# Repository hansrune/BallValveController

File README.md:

# Ball Valve Controller

A DYI ball valve controller for CR05 wiring based on ESP32c3. This device is mainly intended for irrigation and main water valve automation, but is also very suitable for water leak prevention. For safety, a battery helps make sure the device returns to its default state upon reset or power failure. The device can be directly controlled to the default state by external signals such as a local water leak sensor, or you can use your home automation system to cut off water supply based on more advanced conditions.

The default state can be normally open or normally closed, and is automatically detected on restart. The safety battery voltage is also monitored and available to read remotely.

This board is tested with ESPhome and ESPEasy [firmware](#firmwares) (build instructions below), and is easily used with home automation systems that support MQTT auto discovery, the native Home Assistant API, and the many [controllers that ESPEasy supports](https://espeasy.readthedocs.io/en/latest/Controller/_Controller.html)

## Introduction

Some of the main features and benefits

- **Supports 5-wire CR05 wiring**
    - The true state of the valve can be fed back to your automation system over WiFi
    - You can detect valve malfunctioning
    - Is used by the firmware to automatically detect NO (normally open) or NC (normally closed) operation during startup
- **Supports battery backup and battery status monitoring**
    - A 9V battery is sufficient to make sure the valve returns to it's default state during power failure and resets
    - The battery voltage is readable and available as a sensor
- **Water leak sensors and protection**
    - There are inputs to force the valve to the default state as well as the activated state. Typically used with a Fibaro water leak detector associates with a Fibaro smart implant so that the valve can be "overruled" without any host controller / home automation being involved. Numerous Z-wave and Zigbee devices support this.
- **1-wire support**
    - This is used to attach DS18B20 temperature sensor. I use this with a nearby water heater. Two inputs with pull-ups are available, but you can also use multiple sensors on one wire
- **I2C support**
    - An I2C pin header with power supply is available to use with I2C sensors
    - ... or you can use the same GPIO pins for any other purpose of your choise
- **WiFi based**
    - This is almost a must have for most home automation systems
    - OTA support
    - Configuration backup, restore and bulk updates.
- **Firmware of your choise**
    - ESPEasy with Domoticz over http. Device creation uses virtual sensors
    - ESPEasy with Domotics and Home Assistant via MQTT. Device creation uses a MQTT configuration text file.
    - ESPHome to Home Assistant via MQTT and auto discovery
    - ESPHome to Domoticz via MQTT and auto discovery
    - ... and as the hardware supports using both Arduino and ESP-IF development kits, almost any other firmware can be created.
- **Seed Studio XIAO ESP32C3**
    - This device is shielded and comes with an external IPX antenna connector
    - FCC and CE regulations approved

## Setup and mounting

A typical small electic junction box is used for an easy and affordable way for housing the PCB and battery. These boxes often also support using glands for humidity protection and strain releave.

Please note the positioning of the battery. The battery can be easily removed to provide room for a USB-C cable connection, in case an OTA update should fail. Failure to OTA is usually recovered by a power cycle, but bugs in OTA libaries need a physical connection for recovery.

The switch (see wiring below) is used to select between normally open and normally closed operation. As the ball valve will return to it's default position during reset, the valve position feedback switches are used to automatically determine if the setup is normally open or normally closed.

One of my permanent setups look like this:

... where the 1-wire sensors are attached to top and bottom of our electric water boiler.

## Indicators

The 5mm LEDs are suggested to be reverse mounted for the following purposes:

- LED D7 will indicate the state of valve activation - solid on or off
- LED D6
  - will blink with a duty cycle 1-4 or 4-1 to indicate valve closed or open
  - a duty cycle 1:1 will indicate a reset is ongoing
  - no change indicates out of power, device death/freeze or other

## Implementation and design

The easiest way to view the controller is probably this block level wiring diagram:

This is just a typical setup for the various external components. The schematic diagram is [available here](KiCad/BallValveController-schema-7.0.pdf). The [KiCad EDA](https://www.kicad.org/) project is in the [same folder](./KiCad)

If you use more than one 1-wire sensor, it is easier in ESPHome to use both inputs (RX+TX in diagram) with automatic sensor address detection.

### GPIO pin usage

| PIN      | Capabilty          | Function                            |
|----------|--------------------|-------------------------------------|
| GPIO2    | Active low out     | Activate battery read               |
| GPIO3/A1 | Analog in          | Battery read input                  |
| GPIO4    | Active low in      | Valve open                          |
| GPIO5    | Active low in      | Valve closed                        |
| GPIO6    | I2C                | SDA                                 |
| GPIO7    | I2C                | SCL                                 |
| GPIO9    | Active low out     | Internal status LED                 |
| GPIO10   | Active high out    | Valve activate to non-default state |
| GPIO20   | RX / 1-wire        | Serial or 1-wire sensor             |
| GPIO21   | TX / 1-wire        | Serial or 1-wire sensor             |

### Interfacing leak detectors

J10 is used to interface leak detectors:

| PIN  | Name       | Function                              |
|------|------------|---------------------------------------|
| 1    | Activate   | Pull high to force non-default state  |
| 2    | Deactivate | Battery read input                    |
| 3    | Vcc        | Supply voltage, 3.3V, 5V or 12V strap |
| 4    | GND        | Ground                                |

#### Connecting a Fibaro Implant

A Fibaro implant may be associated with Fibaro leak detector(s). This type of device to device can work even without the Z-Wave hub being operational

- `VCC` - strap JP1 to the 12V supply as illustrated [here](#known-bugs), or just feed the Implant directly from the 12V power supply
- `Deactivate` - connect to one side of Out1 - the other side to GND
- `GND` for implant power and Out1

#### Connecting an Arduino water leak sensor

Typical Arduino water leak detectors are open collector outputs. Connect as follows:

- `VCC` - strap/solder JP1 to the 3.3V side for sensor power 
- `Deactivate` - connect to sensor output. This will force the valve to default state when activated
- `GND` - sensor power ground

## Hardware - getting started

This project uses my [KiCad-lib-ESP32 repository](https://github.com/hansrune/KiCad-lib-ESP32.git) as a [git submodule](https://www.git-scm.com/book/en/v2/Git-Tools-Submodules). To check this out, use the following:

```bash
git clone --recurse-submodules https://github.com/hansrune/BallValveController.git 
```

### Materials used

This project uses the [Seed Studio XIAO ESP32C3 RISC-V module](https://www.seeedstudio.com/Seeed-XIAO-ESP32C3-p-5431.html). This tiny device has proven to be more reliable than most ESP8266 modules used in earlier versions. This module also comes with an IPX connector for connecting an external antenna, and is delivered with a simple external antenna for good range. This device is also EMI shielded and certified.

A ball valve like [these HSH-FLO valves](https://www.ebay.com/itm/121728665101?var=420727385309) uses metal gears, and also have a manual override possibility. Despite the moderate cost, I have found them very reliable. Manufacturer claims 100k operations. I typically use a 2 or some times 3-port version, size 3/4" DN20, DC12/24V and with CR05-01 wiring, including a manual overrride whell option.

Any available 12V DC power supply delivering 1A or more should do.

There are many options and possible pinouts for DC-DC converters for the 12V to 5V conversion. A linear regulator (L7805) will need a heatsink, so a DC-DC converter is recommended.

The MOSFETs need a low Vgs trigger voltage, i.e. well under 3V on full load. I have used Si2301/A1SHB for the P-channel, and Si2302/N025P for the N-channel, and 2N2222/1P - all SOT-23 packages.

Resistors are 0805 size. Screw terminals are 3.5mm, which is a tight fit when ferrules are being used.

For more information, use [this KiCad BOM](KiCad/BallValveController-BOM.csv)

## Hardware assembly

Soldering a prototype by hand is possible if you have a steady hand and a small solder iron tip. A microscope is recommended to inspect the solder joints properly.

Recommend to do the SMD parts first, then other components. I prefer to mount the 5mm LEDs on the back side.

### Hardware tests

You should test at least the following **before adding the ESP32 module**:

- Attach a battery and check that the valve can be operated both NO and NC
- Add power and check that 5V conversion is OK
- Apply 5V to the ESP32c3 pin 11 to check that the relay is operated
- Apply 0V to pin 1 of the ESP32c3 and check that pin 2 receives a 200ms readout of the battery voltage (divided by the 68k + 20k resistors)

## Firmwares

### ESPHome

ESPHome firmware can be set up from [this ESPHome configuration repository](https://github.com/hansrune/esphome-config) using the `test_ball_valve` as a template

Follow the [README](https://github.com/hansrune/esphome-config) for instructions on what you will likely want to change.

By default, MQTT auto discovery is being used. This should work out of the box with Home Assistant, Domoticz and other that support [Home Assistant MQTT Auto Discovery](https://www.home-assistant.io/integrations/mqtt/#mqtt-discovery)

In Home Assistant, the device has these controls:

... and information / diagnostics panel:

### ESPEasy

ESPEasy can be used with a number of different controllers / home automation systms. A custom firmware build description is [available here](https://github.com/hansrune/ESPEasy-custom/blob/builds/custom/mega-20240822-1/README-custombuilds.md)

ESPEasy requires many settings. For configuration settings and rule files, you can upload the files from [this page](./ESPEasy/) as a starting point. Please make sure to change name, unit number, controller IP addresses, NTP, syslog host and latitude/longitude. This configuration uses both a MQTT controller and a Domoticz controller. Change to what you need.

## Bugs and tweaks

### For Fibaro Smart Implants

A Fibaro Smart implant needs a 9-30V power supply. To accomodate that, you can supply 12V by running a wire on the back of the PCB as follows:

... or just connect to the 12V input terminal

<!-- 

## How to contribute

-->

## License

This project is licensed under the [GNU General Public License v3.0](GNU-LICENSE-V3.txt) for the software, [CERN-OHL-W](OHL-LICENSE.txt) for the hardware, and [CC BY-SA](CC-BY-SA-LICENCE.txt) for the documentation and ideas.

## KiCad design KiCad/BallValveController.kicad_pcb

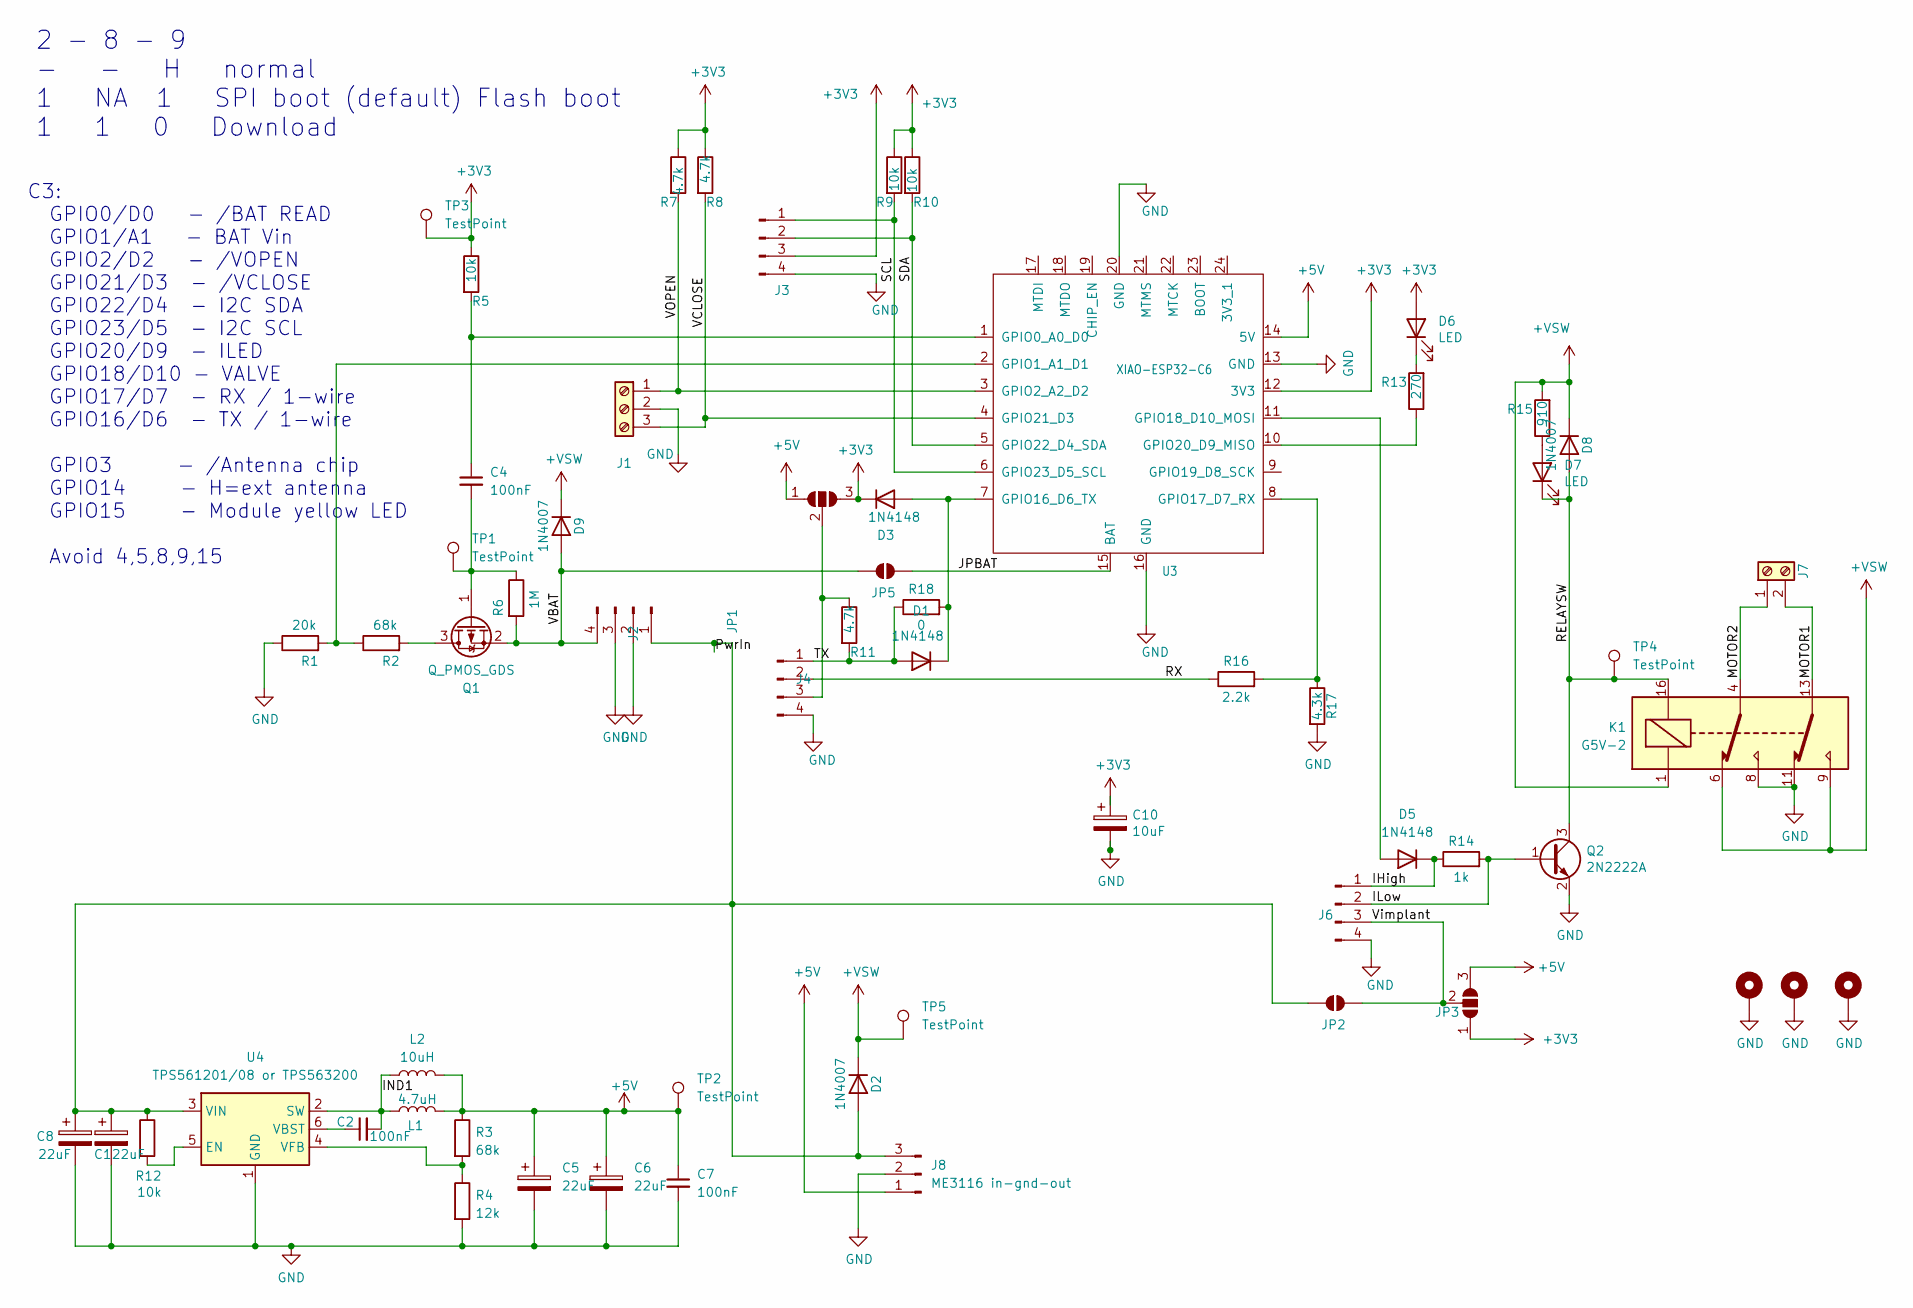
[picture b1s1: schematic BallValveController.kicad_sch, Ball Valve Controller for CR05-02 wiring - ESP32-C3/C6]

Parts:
C1, C8: 22uF; C_1206_3216Metric_Pad1.33x1.80mm_HandSolder
C2, C4, C7: 100nF; C_0805_2012Metric_Pad1.18x1.45mm_HandSolder
C5, C6: 22uF; C_1206_3216Metric_Pad1.33x1.80mm_HandSolder; JLCPCB Part# C45783
C10: 10uF; C_1206_3216Metric_Pad1.33x1.80mm_HandSolder
D1, D3, D5: 1N4148; D_SOD-323_HandSoldering
D2, D8, D9: 1N4007; D_SOD-123
D6, D7: LED; LED_D3.0mm_Clear
H1, H2, H3: MountingHole_Pad; MountingHole_3.2mm_M3_ISO14580_Pad
J1: Screw_Terminal_01x03; TerminalBlock_Phoenix_PT-1,5-3-3.5-H_1x03_P3.50mm_Horizontal
J2, J4, J6: Screw_Terminal_01x04; TerminalBlock_Phoenix_PT-1,5-4-3.5-H_1x04_P3.50mm_Horizontal
J3: Screw_Terminal_01x04; PinHeader_1x04_P2.54mm_Vertical
J7: Screw_Terminal_01x02; TerminalBlock_Phoenix_PT-1,5-2-3.5-H_1x02_P3.50mm_Horizontal
J8: ME3116 in-gnd-out; PinHeader_1x03_P2.54mm_Vertical
JP1, JP3: SolderJumper_3_Open; SolderJumper-3_P1.3mm_Open_Pad1.0x1.5mm_NumberLabels
JP2, JP5: SolderJumper_2_Open; SolderJumper-2_P1.3mm_Open_RoundedPad1.0x1.5mm
K1: G5V-2; Relay_DPDT_Omron_G5V-2
L1: 4.7uH; L_2010_5025Metric_Pad1.52x2.65mm_HandSolder; JLCPCB Part# C2929438
L2: 10uH; L_Bourns-SRU8028_8.0x8.0mm; JLCPCB Part# C2929438
Q1: Q_PMOS_GDS; SOT-23
Q2: 2N2222A; SOT-23
R1: 20k; R_0805_2012Metric_Pad1.20x1.40mm_HandSolder
R2: 68k; R_0805_2012Metric_Pad1.20x1.40mm_HandSolder
R3: 68k; R_0805_2012Metric_Pad1.20x1.40mm_HandSolder; JLCPCB Part# C17850
R4: 12k; R_0805_2012Metric_Pad1.20x1.40mm_HandSolder; JLCPCB Part# C4328
R5, R9, R10: 10k; R_0805_2012Metric_Pad1.20x1.40mm_HandSolder
R6: 1M; R_0805_2012Metric_Pad1.20x1.40mm_HandSolder
R7, R8, R11: 4.7k; R_0805_2012Metric_Pad1.20x1.40mm_HandSolder
R12: 10k; R_0805_2012Metric_Pad1.20x1.40mm_HandSolder; JLCPCB Part# C4328
R13: 270; R_0805_2012Metric_Pad1.20x1.40mm_HandSolder
R14: 1k; R_0805_2012Metric_Pad1.20x1.40mm_HandSolder
R15: 910; R_0805_2012Metric_Pad1.20x1.40mm_HandSolder
R16: 2.2k; R_0805_2012Metric_Pad1.20x1.40mm_HandSolder
R17: 4.3k; R_0805_2012Metric_Pad1.20x1.40mm_HandSolder
R18: 0; R_0805_2012Metric_Pad1.20x1.40mm_HandSolder
TP1, TP2, TP3, TP4, TP5: TestPoint; TestPoint_THTPad_D1.0mm_Drill0.5mm
U3: XIAO-ESP32-C6; XIAO-ESP32-C3C6-SMD
U4: TPS561201/08 or TPS563200; SOT-23-6

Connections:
+3V3: C10.1, D3.1 (K), D6.2 (A), J3.3, JP1.3 (B), JP3.1 (A), R5.1, R7.1, R8.1, R9.1, R10.1, TP3.1 (1_1), U3.12 (3V3)
+5V: C5.1, C6.1, C7.1, J8.1, JP1.1 (A), JP3.3 (B), L1.2, L2.2, R3.1, TP2.1 (1_1), U3.14 (5V)
+VSW: D2.1 (K), D8.1 (K), D9.1 (K), K1.1, K1.6, K1.9, R15.2, TP5.1 (1_1)
/IHigh: D5.1 (K), J6.1, R14.1
/ILow: J6.2, Q2.1 (B), R14.2
/IND1: C2.2, L1.1, L2.1, U4.2 (SW)
/JPBAT: JP5.2 (B), U3.15 (BAT)
/MOTOR1: J7.2, K1.13
/MOTOR2: J7.1, K1.4
/PwrIn: C1.1, C8.1, D2.2 (A), J2.1, J8.3, JP2.1 (A), R12.1, U4.3 (VIN)
/RELAYSW: D7.1 (K), D8.2 (A), K1.16, Q2.3 (C), TP4.1 (1_1)
/RX: J4.2, R16.1
/SCL: J3.1, R9.2, U3.6 (GPIO23_D5_SCL)
/SDA: J3.2, R10.2, U3.5 (GPIO22_D4_SDA)
/TX: D1.2 (A), J4.1, R11.2, R18.1
/VBAT: D9.2 (A), J2.4, JP5.1 (A), Q1.2 (S), R6.2
/VCLOSE: J1.3, R8.2, U3.4 (GPIO21_D3)
/VOPEN: J1.1, R7.2, U3.3 (GPIO2_A2_D2)
/Vimplant: J6.3, JP2.2 (B), JP3.2 (C)
GND: C1.2, C5.2, C6.2, C7.2, C8.2, C10.2, H1.1 (1_1), H2.1 (1_1), H3.1 (1_1), J1.2, J2.2, J2.3, J3.4, J4.4, J6.4, J8.2, K1.8, K1.11, Q2.2 (E), R1.1, R4.2, R17.2, U3.13 (GND), U3.16 (GND), U3.20 (GND), U4.1 (GND)
unnamed: D1.1 (K), D3.2 (A), R18.2, U3.7 (GPIO16_D6_TX)
unnamed: D5.2 (A), U3.11 (GPIO18_D10_MOSI)
unnamed: D6.1 (K), R13.2
unnamed: D7.2 (A), R15.1
unnamed: J4.3, JP1.2 (C), R11.1
unnamed: Q1.3 (D), R2.2
unnamed: C4.2, Q1.1 (G), R6.1, TP1.1 (1_1)
unnamed: C4.1, R5.2, U3.1 (GPIO0_A0_D0)
unnamed: R1.2, R2.1, U3.2 (GPIO1_A1_D1)
unnamed: R16.2, R17.1, U3.8 (GPIO17_D7_RX)
unnamed: R13.1, U3.10 (GPIO20_D9_MISO)
unnamed: R12.2, U4.5 (EN)
unnamed: C2.1, U4.6 (VBST)
unnamed: R3.2, R4.1, U4.4 (VFB)

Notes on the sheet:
2 - 8 - 9 - - H normal 1 NA 1 SPI boot (default) Flash boot 1 1 0 Download
C3: GPIO0/D0 - /BAT READ GPIO1/A1 - BAT Vin GPIO2/D2 - /VOPEN GPIO21/D3 - /VCLOSE GPIO22/D4 - I2C SDA GPIO23/D5 - I2C SCL GPIO20/D9 - ILED GPIO18/D10 - VALVE GPIO17/D7 - RX / 1-wire GPIO16/D6 - TX / 1-wire GPIO3 - /Antenna chip GPIO14 - H=ext antenna GPIO15 - Module yellow LED Avoid 4,5,8,9,15

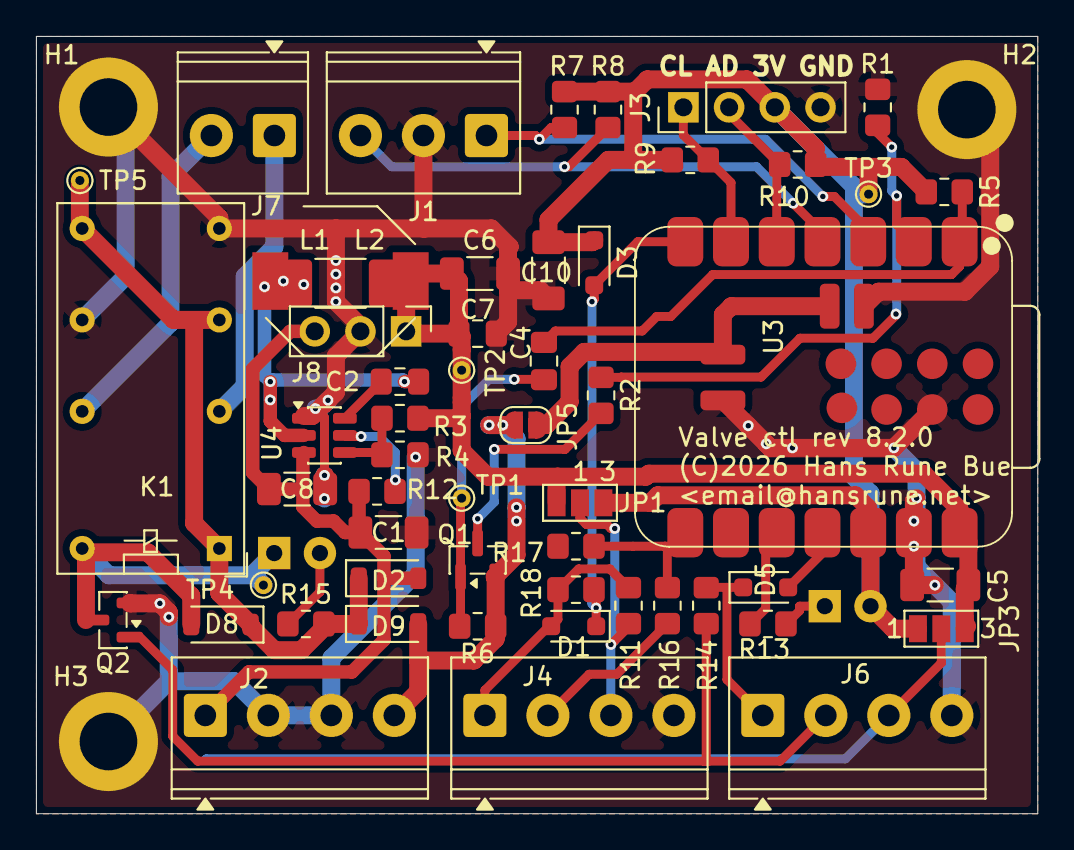
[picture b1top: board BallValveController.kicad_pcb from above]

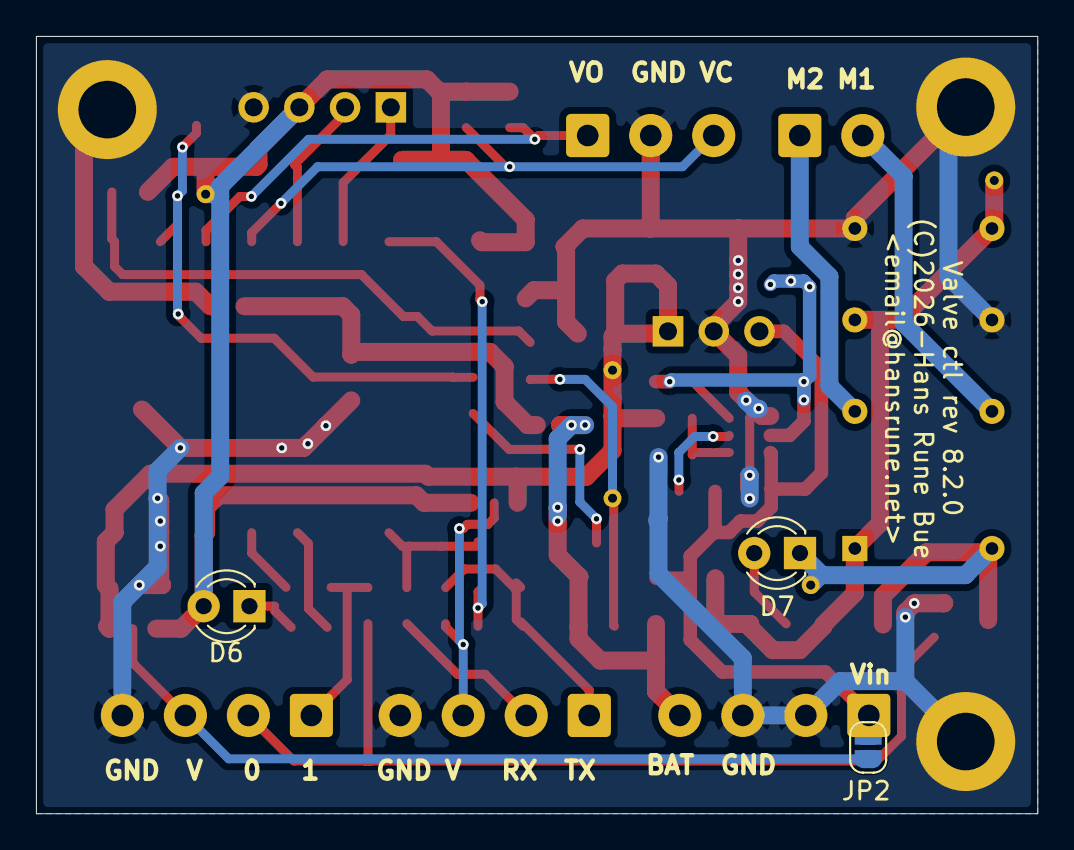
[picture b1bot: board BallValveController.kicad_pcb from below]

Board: 2 copper layers, 55.6 x 43.2 mm, 60 parts (3 on the bottom side), 34 nets.

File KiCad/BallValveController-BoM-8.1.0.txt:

|Reference|||Value|||Datasheet|||Footprint|||Qty|||DNP|
|C1 C5 C6 C8|||22uF|||~|||Capacitor_SMD:C_1206_3216Metric_Pad1.33x1.80mm_HandSolder|||4||||
|C2 C4 C7|||100nF|||~|||Capacitor_SMD:C_0805_2012Metric_Pad1.18x1.45mm_HandSolder|||3||||
|C10|||10uF|||~|||Capacitor_SMD:C_1206_3216Metric_Pad1.33x1.80mm_HandSolder|||1||||
|D1 D3 D5|||1N4148|||~|||Diode_SMD:D_SOD-323_HandSoldering|||3||||
|D2 D8 D9|||1N4007|||http://www.vishay.com/docs/88503/1n4001.pdf|||Diode_SMD:D_SOD-123|||3||||
|D6 D7|||LED|||~|||LED_THT:LED_D3.0mm_Clear|||2||||
|H1 H2 H3|||MountingHole_Pad|||~|||MountingHole:MountingHole_3.2mm_M3_ISO14580_Pad|||3||||
|J1|||Screw_Terminal_01x03|||~|||TerminalBlock_Phoenix:TerminalBlock_Phoenix_PT-1,5-3-3.5-H_1x03_P3.50mm_Horizontal|||1||||
|J2 J3 J4 J6|||Screw_Terminal_01x04|||~|||Connector_PinHeader_2.54mm:PinHeader_1x04_P2.54mm_Vertical,TerminalBlock_Phoenix:TerminalBlock_Phoenix_PT-1,5-4-3.5-H_1x04_P3.50mm_Horizontal|||4||||
|J5|||Conn_01x01_Male|||~|||Connector_PinHeader_2.54mm:PinHeader_1x01_P2.54mm_Vertical|||1||||
|J7|||Screw_Terminal_01x02|||~|||TerminalBlock_Phoenix:TerminalBlock_Phoenix_PT-1,5-2-3.5-H_1x02_P3.50mm_Horizontal|||1||||
|JP1 JP3|||SolderJumper_3_Open|||~|||Jumper:SolderJumper-3_P1.3mm_Open_Pad1.0x1.5mm_NumberLabels|||2||||
|K1|||G5V-2|||http://omronfs.omron.com/en_US/ecb/products/pdf/en-g5v_2.pdf|||Relay_THT:Relay_DPDT_Omron_G5V-2|||1||||
|L1|||4.7uH|||~|||Inductor_SMD:L_2010_5025Metric_Pad1.52x2.65mm_HandSolder|||1||||
|L2|||10uH|||~|||Inductor_SMD:L_Bourns-SRU8028_8.0x8.0mm|||1||||
|Q1|||Q_PMOS_GDS||||||Package_TO_SOT_SMD:SOT-23|||1||||
|Q2|||2N2222A||||||Package_TO_SOT_SMD:SOT-23|||1||||
|R1|||20k|||~|||Resistor_SMD:R_0805_2012Metric_Pad1.20x1.40mm_HandSolder|||1||||
|R2 R3|||68k|||~|||Resistor_SMD:R_0805_2012Metric_Pad1.20x1.40mm_HandSolder|||2||||
|R4|||12k|||~|||Resistor_SMD:R_0805_2012Metric_Pad1.20x1.40mm_HandSolder|||1||||
|R5 R9 R10 R12|||10k|||~|||Resistor_SMD:R_0805_2012Metric_Pad1.20x1.40mm_HandSolder|||4||||
|R6|||1M|||~|||Resistor_SMD:R_0805_2012Metric_Pad1.20x1.40mm_HandSolder|||1||||
|R7 R8 R11|||4.7k|||~|||Resistor_SMD:R_0805_2012Metric_Pad1.20x1.40mm_HandSolder|||3||||
|R13|||270|||~|||Resistor_SMD:R_0805_2012Metric_Pad1.20x1.40mm_HandSolder|||1||||
|R14|||1k|||~|||Resistor_SMD:R_0805_2012Metric_Pad1.20x1.40mm_HandSolder|||1||||
|R15|||910|||~|||Resistor_SMD:R_0805_2012Metric_Pad1.20x1.40mm_HandSolder|||1||||
|R16|||2.2k|||~|||Resistor_SMD:R_0805_2012Metric_Pad1.20x1.40mm_HandSolder|||1||||
|R17|||4.3k|||~|||Resistor_SMD:R_0805_2012Metric_Pad1.20x1.40mm_HandSolder|||1||||
|R18|||0|||~|||Resistor_SMD:R_0805_2012Metric_Pad1.20x1.40mm_HandSolder|||1||||
|U2|||L7805|||http://www.st.com/content/ccc/resource/technical/document/da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|||Package_TO_SOT_THT:TO-220-3_Vertical|||1||||
|U3|||XIAO-ESP32-C6||||||LOCAL1:XIAO-ESP32-C3C6-SMD|||1||||
|U4|||TPS561201/08 or TPS563200|||http://www.ti.com/lit/ds/symlink/tps563200.pdf|||Package_TO_SOT_SMD:SOT-23-6|||1||||

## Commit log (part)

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2024-06-03 Added KiCad files and KiCad images
2024-06-03 Add licensing
2024-06-03 README updates
2024-06-03 FOrmatting
2024-06-03 More docs
2024-06-17 Change image size
2024-06-17 Renamed license files
2024-06-17 Renamed images
2024-06-17 Images resized
2024-06-17 DC-DC converter options
2024-06-17 Use image size in px
2024-06-17 resized images
2024-06-20 Main README updates
2024-06-24 v7.0.1 - updated metadata only
2024-08-30 Added interfacing and firmwares sections
2024-09-04 ESPEasy config and rule files added
2024-09-04 Added Home Assistant screenshots + description
2024-09-04 Initial statements reordered
2024-09-19 New 3D model
2024-10-07 README about OTA failures
2025-03-24 Add LICENSE overview file
2025-10-15 First ESP32C6 layout
2025-10-16 DRC of esp32c6 done
2025-10-16 Add the LOCAL1 footprint library relative to
2025-10-16 DRC fill was deleted
2025-10-17 Added step down converter
2025-10-20 New diode footprints
2025-10-26 Footprint change 1N4148 to SOD-323
2025-10-26 New layout - changed Diodes and Cap footprints + RX/TX wiring
2025-10-28 Version 8.0.2 pdf files
2025-11-24 Fixed MT2499A layout
2025-11-24 DRC with TPC561201/08
2025-12-19 Added EN resistor for buck converter
2025-12-19 8.1.0 print files added
2025-12-25 Print, Gerbers for v8.1.0
2026-01-02 Small layout change for buck feedback loop
2026-01-04 Rearranged resistors - stricter fill clearances
2026-01-05 GND zones update
2026-03-22 ME3116 layout
2026-04-20 ME3116 dual layout
2026-04-20 Add ME3116 support via 1x3 pin header
2026-05-06 Move DCDC converter up, inductor down

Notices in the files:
KiCad/BallValveController.kicad_pcb:
(C)2026 Hans Rune Bue
KiCad/BallValveController.kicad_sch:
Copyright - Hans Rune Bue
Hardware is licensed under CERN-OHL-W-2.0
Project documents are licensed under CC-BY-SA 2.0
